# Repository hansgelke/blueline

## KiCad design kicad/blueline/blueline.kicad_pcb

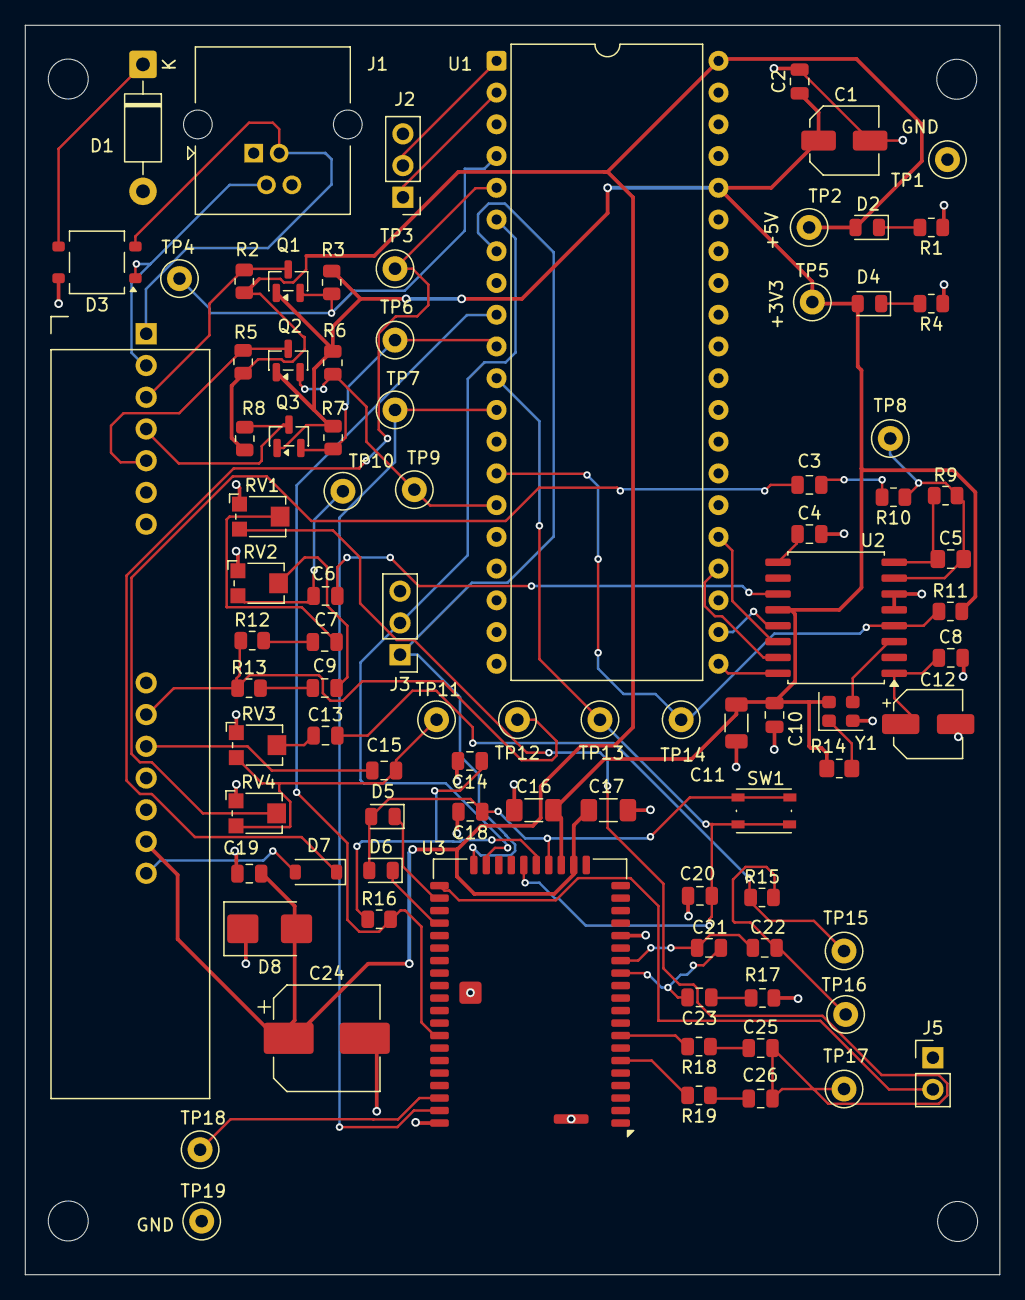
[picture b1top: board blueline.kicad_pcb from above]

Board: 4 copper layers, 78.0 x 100.0 mm, 93 parts (0 on the bottom side), 62 nets.

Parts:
C1: 100uF/10V; C_Elec_5x5.4
C2, C4, C8, C10, C14, C18, C19, C22, C23: 100nF; C_0805_2012Metric
C3, C6, C7, C9, C13, C15, C25, C26: 470nF; C_0805_2012Metric
C5: 100p; C_0805_2012Metric_Pad1.18x1.45mm_HandSolder
C11: 4.7uF; C_1206_3216Metric
C12: 10uF/16V; CP_Elec_5x3
C16, C17: 1uF; C_1206_3216Metric_Pad1.33x1.80mm_HandSolder
C20: 100pF; C_0805_2012Metric
C21: 220pF; C_0805_2012Metric
C24: 470uF/16V; CP_Elec_8x6.5
D1: BZT03C82; D_DO-41_SOD81_P10.16mm_Horizontal
D2, D4: LED; LED_0805_2012Metric
D3: MB4S; TO-269AA
D5: LED RED; LED_0805_2012Metric
D6: LED BLUE; LED_0805_2012Metric
D7: 1N4148; D_SOD-123
D8: P6SMB10CA; D_SMB
He1, He2, He3, He4: MountingHole; MountingHole_3.2mm_M3
J1: RJ14; RJ14_Connfly_DS1133-S4_Horizontal
J2, J3: Conn_01x03_Pin; PinHeader_1x03_P2.54mm_Vertical
J4: AG1171; AG1172_foot
J5: Conn_01x02_Pin; PinHeader_1x02_P2.54mm_Vertical
Q1, Q2, Q3: 2N7002; SOT-23
R1: 330; R_0805_2012Metric
R2, R3, R5, R6, R7, R8, R11, R16: 10k; R_0805_2012Metric
R4: 220; R_0805_2012Metric
R9, R15, R17: 100k; R_0805_2012Metric
R10: 150k; R_0805_2012Metric
R12, R13: 47k; R_0805_2012Metric
R14: 10k; R_0805_2012Metric_Pad1.20x1.40mm_HandSolder
R18, R19: 1k; R_0805_2012Metric
RV1, RV2, RV3, RV4: 10k; Potentiometer_Bourns_TC33X_Vertical
SW1: SW_Push; SW_Push_1P1T_NO_Vertical_Wuerth_434133025816
TP1, TP2, TP3, TP4, TP5, TP6, TP7, TP8, TP9, TP10, TP11, TP12, TP13, TP14, TP15, TP16, TP17, TP18, TP19: TestPoint; TestPoint_Loop_D2.50mm_Drill1.0mm
U1: Pico2_foot
U2: SOIC-16W_7.5x10.3mm_P1.27mm
U3: Microchip_BM83
Y1: SiT8008B 6.144 MHz; Oscillator_SMD_SiT_PQFN-4Pin_2.5x2.0mm

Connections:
+3V3: C1.1, C2.1, C10.1, C11.1, C16.1, D4.2 (A), Q1.1 (G), Q2.1 (G), Q3.1 (G), R3.2, R6.2, R7.2, R11.2, R14.1, TP5.1 (1_1), U1.36 (3V3(OUT)), U2.12 (VDD), U3.23 (BAT_IN), Y1.4 (Vdd)
+5V: C17.1, C19.1, C24.1, D2.2 (A), D8.2 (A2), J4.13, R2.2, R5.2, R8.2, TP2.1 (1_1), U1.40 (VBUS), U3.22 (ADAP_IN)
/BT_INT: TP7.1 (1_1), U1.12 (GP9), U3.49 (P0_0/UART_TX_IND)
/BT_MFB: C20.1, SW1.2, TP13.1 (1_1), U1.11 (GP8), U3.26 (PWR(MFB))
/BT_RXD: J3.2, U1.6 (GP4), U3.29 (P8_6/UART_RXD)
/BT_TXD: J3.1, U1.7 (GP5), U3.30 (P8_5/UART_TXD)
/POT_CS_N: U1.22 (GP17), U2.13 (CSN)
/POT_FWD: Q1.2 (S), R3.1, TP4.1 (1_1), U1.4 (GP2)
/POT_INT_N: R11.1, TP14.1 (1_1), U1.14 (GP10), U2.4 (IRQN)
/POT_MISO: U1.21 (GP16), U2.16 (MISO)
/POT_MOSI: U1.25 (GP19), U2.14 (MOSI)
/POT_PDOWN_N: D7.1 (K), TP3.1 (1_1), U1.5 (GP3)
/POT_RING: Q3.2 (S), R7.1, TP6.1 (1_1), U1.10 (GP7)
/POT_SCLK: U1.24 (GP18), U2.15 (SCLK)
/POT_SHK: Q2.2 (S), R6.1, TP9.1 (1_1), U1.15 (GP11)
/RESET_N: R16.2, U1.9 (GP6), U3.43 (~RST)
/blueline_pots/POT_AUD_IN: C25.2, C26.2, RV1.3, TP17.1 (1_1)
/blueline_pots/POT_AUD_OUT: C13.2, R15.1, TP15.1 (1_1)
/blueline_pots/level_converter1/IO_5V: J4.3, Q1.3 (D), R2.1
/blueline_pots/level_converter2/IO_5V: J4.5, Q2.3 (D), R5.1
/blueline_pots/level_converter/IO_5V: J4.4, Q3.3 (D), R8.1
GND: C1.2, C2.2, C4.2, C8.2, C10.2, C11.2, C12.2, C14.2, C16.2, C17.2, C18.2, C19.2, C20.2, C24.2, D1.2 (A), D3.4 (-), D8.1 (A1), J2.3, J3.3, J4.12, J5.1, R1.1, R4.1, R17.1, RV1.1, RV2.1, RV3.1, RV4.1, TP1.1 (1_1), TP19.1 (1_1), U1.3 (GND), U1.8 (GND), U1.13 (GND), U1.18 (GND), U1.23 (GND), U1.28 (GND), U1.33 (GND), U1.38 (GND), U2.5 (VSSD), U2.6 (VSSA), U3.16 (GND), U3.50 (GND), U3.56 (GND), U3.57 (GND), Y1.2 (GND)
unnamed: C3.1, R10.2
unnamed: C3.2, RV4.2
unnamed: C6.2, RV2.3, TP10.1 (1_1)
unnamed: C7.1, RV1.2
unnamed: C7.2, R12.2
unnamed: C9.1, RV2.2
unnamed: C9.2, R13.2
unnamed: C13.1, RV3.2
unnamed: C15.2, RV3.3, RV4.3, TP11.1 (1_1)
unnamed: C22.1, R15.2, TP16.1 (1_1)
unnamed: C23.1, R17.2
unnamed: C25.1, R18.1
unnamed: C26.1, R19.1
unnamed: D1.1 (K), D3.3 (+)
unnamed: D2.1 (K), R1.2
unnamed: D4.1 (K), R4.2
unnamed: C18.1, D5.2 (A), D6.2 (A), SW1.1, U3.24 (SYS_PWR)
unnamed: D5.1 (K), U3.32 (LED1)
unnamed: D6.1 (K), U3.34 (LED2)
unnamed: D7.2 (A), J4.14
unnamed: J2.1, U1.2 (GP1)
unnamed: J2.2, U1.1 (GP0)
unnamed: D3.2, J1.3, J4.1
unnamed: D3.1, J1.2, J4.2
unnamed: J4.9, R12.1, R13.1, TP12.1 (1_1)
unnamed: C15.1, J4.10
unnamed: J5.2, U3.31 (P3_4/UART_RTS)
unnamed: C5.2, R9.2, R10.1, TP8.1 (1_1), U2.7 (RXAN)
unnamed: C5.1, R9.1, U2.8 (RXFB)
unnamed: C6.1, U2.11 (TXA)
unnamed: C4.1, U2.9 (VBIAS)
unnamed: C8.1, C12.1, U2.1 (VDEC)
unnamed: U2.3 (XTAL), Y1.3 (OUT)
unnamed: R18.2, U3.8 (AOHPL)
unnamed: R19.2, U3.6 (AOHPR)
unnamed: C21.1, C23.2, U3.13 (MICN1)
unnamed: C21.2, C22.2, U3.14 (MICP1)
unnamed: TP18.1 (1_1), U3.48 (P3_7/UART_CTS)
unnamed: C14.1, R16.1, U3.25 (VDD_IO)
unnamed: R14.2, Y1.1 (OE)

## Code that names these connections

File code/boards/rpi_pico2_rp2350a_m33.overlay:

/*
 * blueline - devicetree overlay for rpi_pico2/rp2350a/m33
 *
 * Only changes to the stock board devicetree are listed here. The stock board
 * already provides: gpio0, console on uart0 (GPIO0 TX / GPIO1 RX) and the user
 * LED led0 on GPIO25.
 *
 * GPIO usage of this project. The pins are configured at runtime in
 * src/pico_io.c, not through devicetree nodes:
 *
 *   GPIO2   POT_FWD_PIN      SLIC, PWM1 output (slice 1 A), 25 Hz, high = ringer off (src/ring.c)
 *   GPIO3   POT_PDOWN_N_PIN  SLIC power down, tristate after init (src/slic.c)
 *   GPIO6   BT_RST_N_PIN     output (BM83 reset, src/bm_83.c), low after init
 *   GPIO7   RING_MODE_PIN    SLIC, output, low after init (src/slic.c)
 *   GPIO8   BT_MFB_PIN       output (BM83 MFB, src/bm_83.c), low after init
 *   GPIO11  SHK_RISING_PIN   input, no pulls, IRQ on rising edge
 *   GPIO12  SHK_FALLING_PIN  input, no pulls, IRQ on falling edge
 *   GPIO25  PICO_IO_LED_PIN  output, user LED, high = on
 *
 * UART1 to the Microchip BM83 Bluetooth module (src/bt_uart.c):
 *
 *   GPIO4   UART1 TX  (RP2350 -> BM83)
 *   GPIO5   UART1 RX  (BM83 -> RP2350)
 *   115200 baud, 8N1, no flow control
 */

/* pico_io.c uses gpio0 directly (DT_NODELABEL(gpio0)) */
&gpio0 {
	status = "okay";
};

/* The stock board enables i2c0 (GPIO4/5) and i2c1 (GPIO6/7). These pins are
 * used here for UART1 and RING_MODE, so both I2C controllers are disabled. */
&i2c0 {
	status = "disabled";
};

&i2c1 {
	status = "disabled";
};

&pinctrl {
	/* ringer PWM: PWM slice 1 channel A on GP2 (POT_FWD) */
	pwm_ch1a_default: pwm_ch1a_default {
		group1 {
			pinmux = <PWM_1A_P2>;
		};
	};

	uart1_default: uart1_default {
		group1 {
			pinmux = <UART1_TX_P4>;
		};
		group2 {
			pinmux = <UART1_RX_P5>;
			input-enable;
		};
	};
};

/* BM83 link, no hw-flow-control property = no RTS/CTS */
&uart1 {
	status = "okay";
	current-speed = <115200>;
	pinctrl-0 = <&uart1_default>;
	pinctrl-names = "default";
};

/* Ringer PWM (src/ring.c). Replaces the board default pinctrl (PWM 4B on the
 * user LED GP25), so GP25 stays a GPIO. */
&pwm {
	status = "okay";
	pinctrl-0 = <&pwm_ch1a_default>;
	pinctrl-names = "default";
};
